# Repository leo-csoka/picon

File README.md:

# picon
**picon** is an effort to emulate a Joy-Con using the original Raspberry Pi Pico W. This includes Bluetooth Classic HID support and a wired connection to the Switch. More information will be available soon.

## repository structure
```text
.
├── .gitignore
├── build.sh
├── CMakeLists.txt
├── LICENSE
├── pico_sdk_import.cmake
├── push.sh
├── README.md
├── src/
│   ├── btstack_config.h
│   ├── btstack_config_common.h
│   ├── joycon.c
│   ├── joycon.h
│   ├── joycon_bt.c
│   ├── joycon_bt.h
│   ├── joycon_descriptor.c
│   ├── joycon_descriptor.h
│   └── main.c
├── kicad/
│   ├── module/
│   │   └── kicad project files
│   ├── ribbon-breakout/
│   │   └── FPC breakout for prototyping
│   └── smd-board/
│       └── kicad project files
├── tests/
│   └── keyboard_demo.py
└── TODO.txt
```

**last updated**: Nov 16, 2026

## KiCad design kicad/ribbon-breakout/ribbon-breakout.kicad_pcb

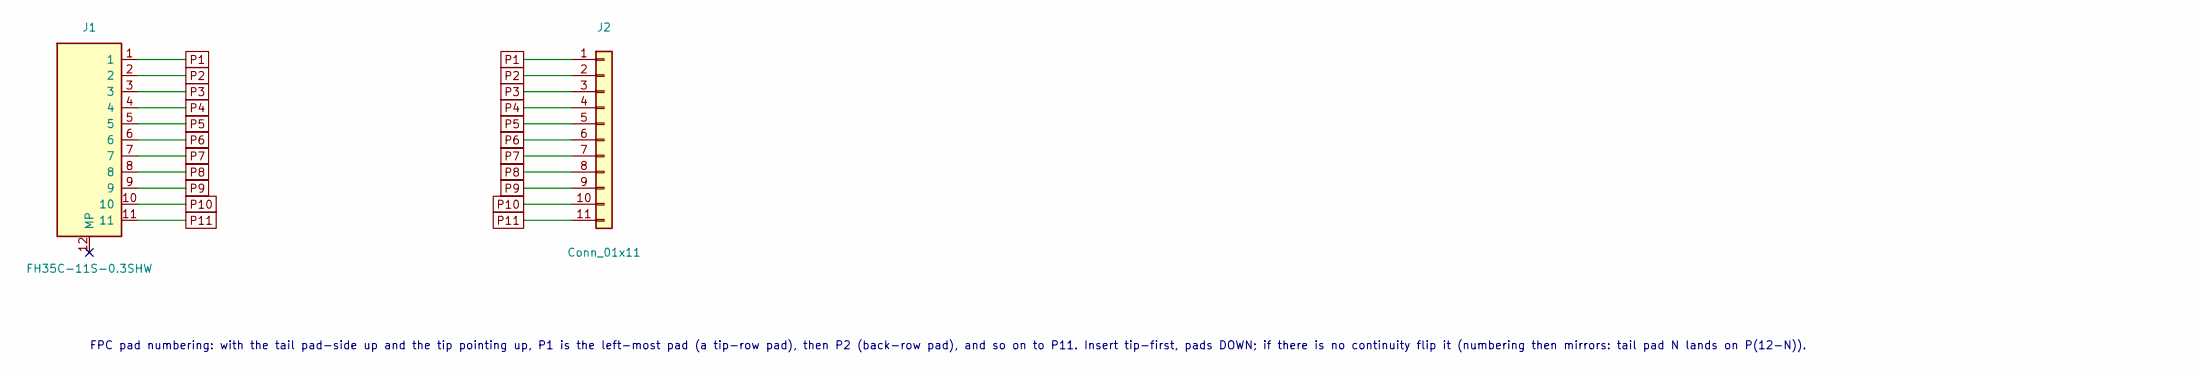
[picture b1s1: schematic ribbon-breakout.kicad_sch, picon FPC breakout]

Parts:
J1: FH35C-11S-0.3SHW; LCSC C5741856
J2: Conn_01x11; PinHeader_1x11_P2.54mm_Vertical

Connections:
P1: J1.1, J2.1
P2: J1.2, J2.2
P3: J1.3, J2.3
P4: J1.4, J2.4
P5: J1.5, J2.5
P6: J1.6, J2.6
P7: J1.7, J2.7
P8: J1.8, J2.8
P9: J1.9, J2.9
P10: J1.10, J2.10
P11: J1.11, J2.11

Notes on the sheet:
FPC pad numbering: with the tail pad-side up and the tip pointing up, P1 is the left-most pad (a tip-row pad), then P2 (back-row pad), and so on to P11. Insert tip-first, pads DOWN; if there is no continuity flip it (numbering then mirrors: tail pad N lands on P(12-N)).

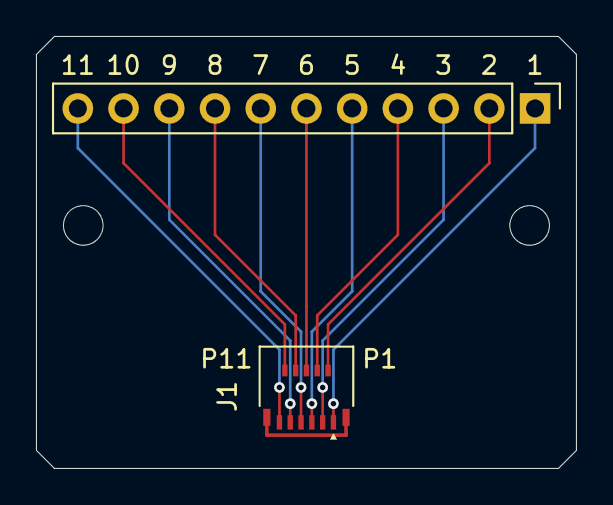
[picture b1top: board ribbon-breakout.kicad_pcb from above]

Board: 2 copper layers, 30.0 x 24.0 mm, 4 parts (0 on the bottom side), 11 nets.

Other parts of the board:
H1, H2: MountingHole_2.2mm_M2

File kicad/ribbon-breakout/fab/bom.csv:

Comment,Designator,Footprint,JLCPCB Part #
FH35C-11S-0.3SHW(99),J1,FPC-SMD_FH35C-11S-0.3SHW,C5741856
PZ254V-11-11P,J2,HDR-TH_11P-P2.54-V-M,C2840011

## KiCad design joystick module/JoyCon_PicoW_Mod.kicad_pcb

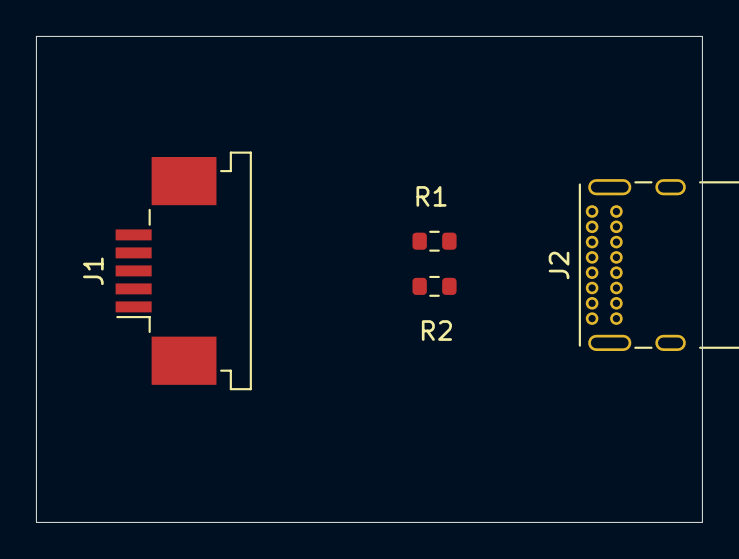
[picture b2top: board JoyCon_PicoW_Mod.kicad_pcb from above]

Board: 2 copper layers, 37.0 x 27.0 mm, 4 parts (0 on the bottom side), 4 nets, no tracks yet.

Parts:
J1: Conn_01x05_Socket; TE_84953-5_1x05-1MP_P1.0mm_Horizontal
J2: USB_C_Receptacle_USB2.0_16P; USB_C_Receptacle_GCT_USB4085
R1, R2: 5.1k ohms; R_0603_1608Metric

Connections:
GND: J1.4, J1.5, J2.A1 (GND), J2.A5 (CC1), J2.A7 (D-), J2.A12 (GND), J2.B1 (GND), J2.B5 (CC2), J2.B7 (D-), J2.B12 (GND), J2.SH (SHIELD), R1.1, R1.2, R2.1, R2.2
unnamed: J1.1, J2.A4 (VBUS), J2.A9 (VBUS), J2.B4 (VBUS), J2.B9 (VBUS)
unnamed: J1.2, J2.A6 (D+), J2.B6 (D+)
unnamed: J1.3, J2.A8 (SBU1)
